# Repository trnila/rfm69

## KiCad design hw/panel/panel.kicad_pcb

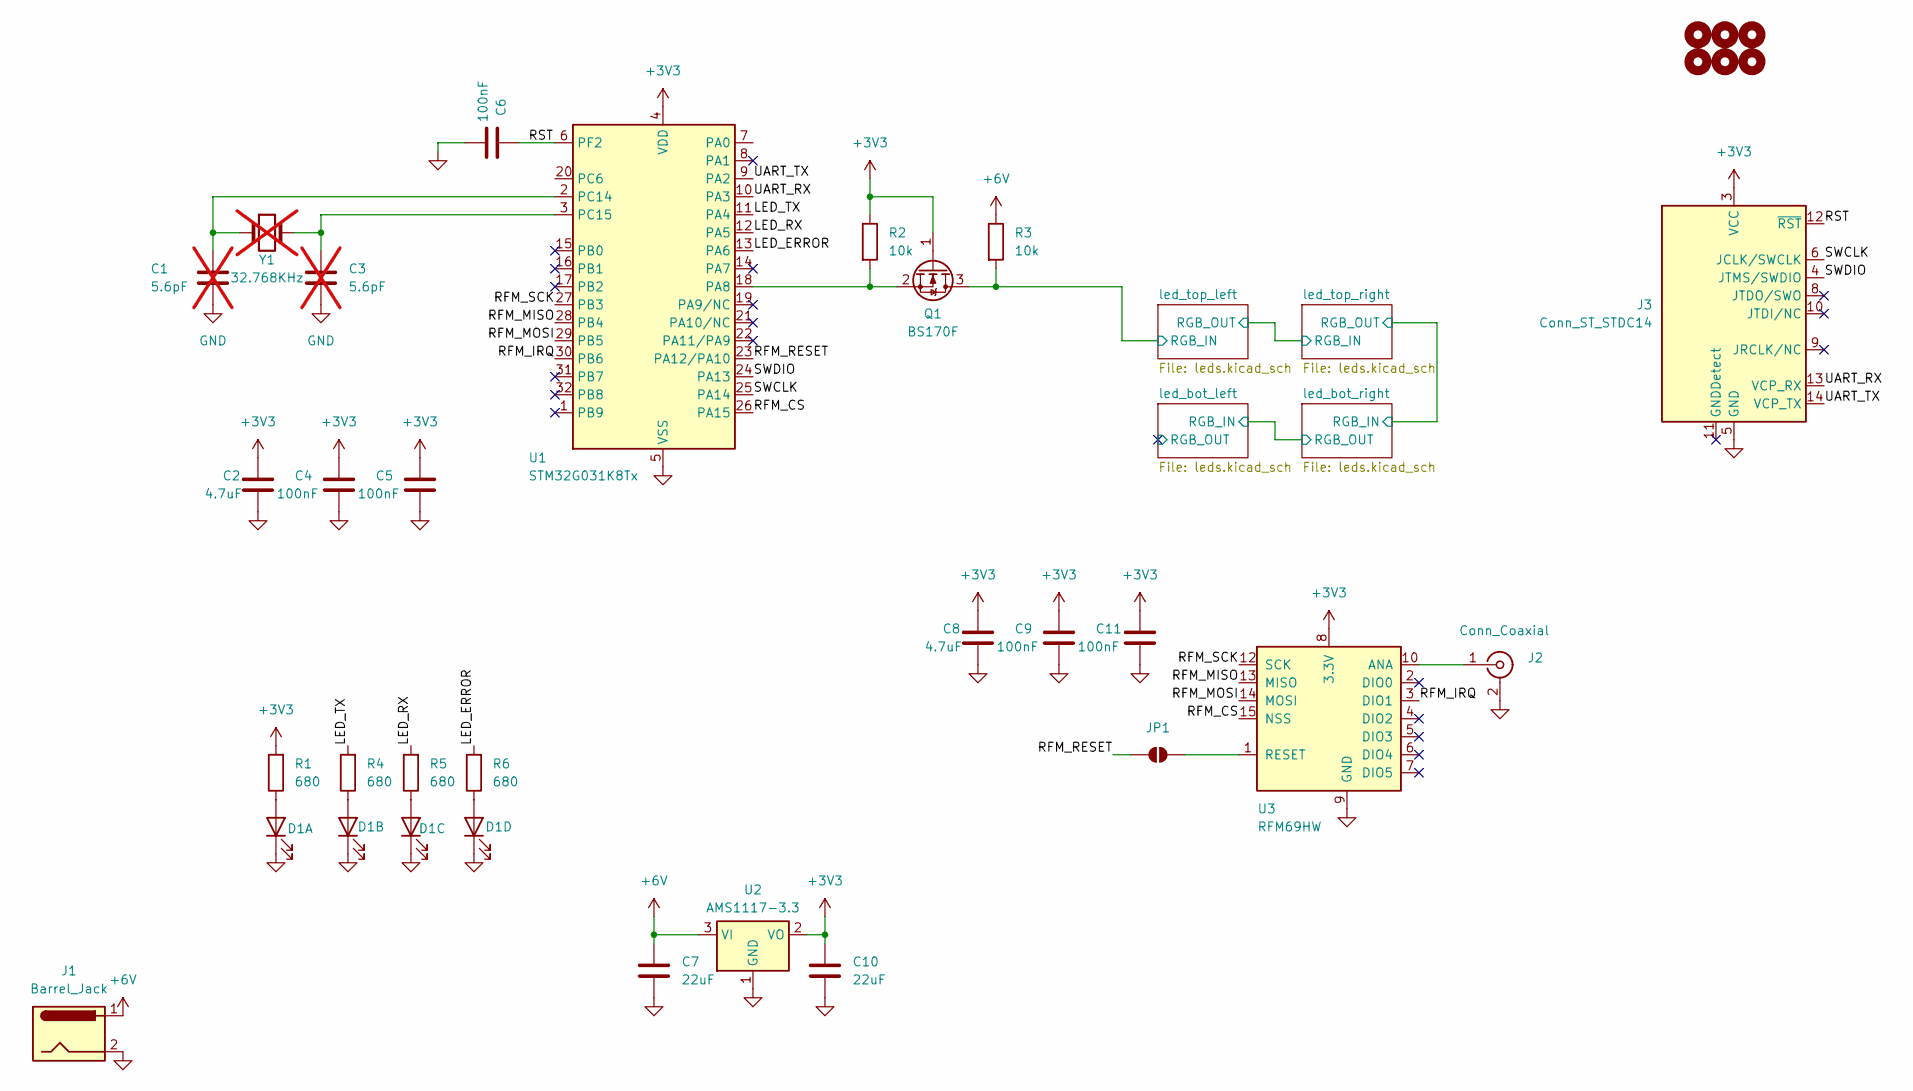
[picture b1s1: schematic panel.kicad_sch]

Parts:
C1, C3: 5.6pF; C_0805_2012Metric_Pad1.18x1.45mm_HandSolder; not fitted
C2, C8: 4.7uF; C_0805_2012Metric_Pad1.18x1.45mm_HandSolder
C4, C5, C6, C9, C11: 100nF; C_0805_2012Metric_Pad1.18x1.45mm_HandSolder
C7, C10: 22uF; C_1210_3225Metric
D1: light_guide
H1, H2, H3, H4, H200, H201: MountingHole; MountingHole_3.2mm_M3
J1: Barrel_Jack; Molex_Micro-Fit_3.0_43650-0200_1x02_P3.00mm_Horizontal
J2: Conn_Coaxial; SMA_Amphenol_901-143_Horizontal
J3: Conn_ST_STDC14; PinHeader_2x07_P1.27mm_Horizontal
JP1: SolderJumper_2_Bridged; SolderJumper-2_P1.3mm_Open_TrianglePad1.0x1.5mm
Q1: BS170F; SOT-23
R1, R4, R5, R6: 680; R_0805_2012Metric_Pad1.20x1.40mm_HandSolder
R2, R3: 10k; R_0805_2012Metric_Pad1.20x1.40mm_HandSolder
U1: STM32G031K8Tx; LQFP-32_7x7mm_P0.8mm
U2: AMS1117-3.3; SOT-223-3_TabPin2
U3: RFM69HW; HOPERF_RFM69HW
Y1: 32.768KHz; Crystal_SMD_3215-2Pin_3.2x1.5mm; not fitted

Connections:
+3V3: C2.1, C4.1, C5.1, C8.1, C9.1, C10.1, C11.1, J3.3 (VCC), Q1.1 (G), R1.2, R2.1, U1.4 (VDD), U2.2 (VO), U3.8 (3.3V)
+6V: C7.1, J1.1, R3.1, U2.3 (VI); also elsewhere on the board
/LED_ERROR: R6.2, U1.13 (PA6)
/LED_RX: R5.2, U1.12 (PA5)
/LED_TX: R4.2, U1.11 (PA4)
/RFM_CS: U1.26 (PA15), U3.15 (NSS)
/RFM_IRQ: U1.30 (PB6), U3.3 (DIO1)
/RFM_MISO: U1.28 (PB4), U3.13 (MISO)
/RFM_MOSI: U1.29 (PB5), U3.14 (MOSI)
/RFM_RESET: JP1.2 (B), U1.23 (PA12/PA10)
/RFM_SCK: U1.27 (PB3), U3.12 (SCK)
/RST: C6.1, J3.12 (~RST), U1.6 (PF2)
/SWCLK: J3.6 (JCLK/SWCLK), U1.25 (PA14)
/SWDIO: J3.4 (JTMS/SWDIO), U1.24 (PA13)
/UART_RX: J3.13 (VCP_RX), U1.10 (PA3)
/UART_TX: J3.14 (VCP_TX), U1.9 (PA2)
/led_top_left/RGB_IN: Q1.3 (D), R3.2; also elsewhere on the board
GND: C1.2, C2.2, C3.2, C4.2, C5.2, C6.2, C7.2, C8.2, C9.2, C10.2, C11.2, D1.1 (K), D1.3 (K), D1.5 (K), D1.7 (K), J1.2, J2.2 (Ext), J3.5 (GND), J3.7 (GND), U1.5 (VSS), U2.1 (GND), U3.9 (GND), U3.11 (GND); also elsewhere on the board
unnamed: D1.2 (A), R1.1
unnamed: D1.4 (A), R4.1
unnamed: D1.6 (A), R5.1
unnamed: D1.8 (A), R6.1
unnamed: J2.1 (In), U3.10 (ANA)
unnamed: JP1.1 (A), U3.1 (RESET)
unnamed: Q1.2 (S), R2.2, U1.18 (PA8)
unnamed: C1.1, U1.2 (PC14), Y1.1
unnamed: C3.1, U1.3 (PC15), Y1.2

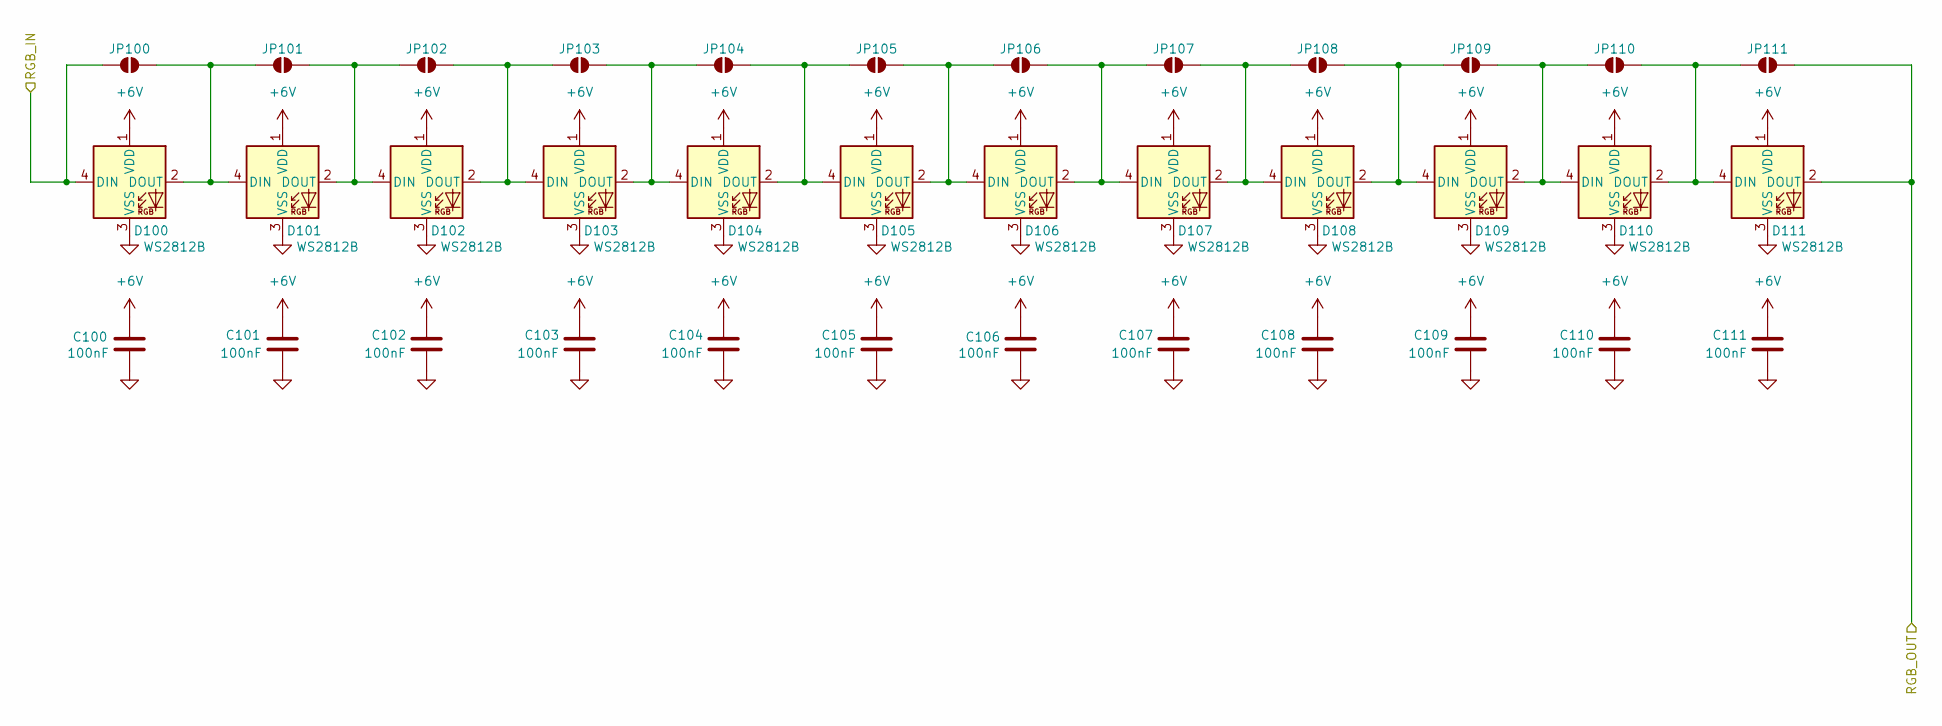
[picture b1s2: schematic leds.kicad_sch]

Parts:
C100, C101, C102, C103, C104, C105, C106, C107, C108, C109, C110, C111: 100nF; C_0805_2012Metric_Pad1.18x1.45mm_HandSolder
D100, D101, D102, D103, D104, D105, D106, D107, D108, D109, D110, D111: WS2812B; LED_WS2812B_PLCC4_5.0x5.0mm_P3.2mm
JP100, JP101, JP102, JP103, JP104, JP105, JP106, JP107, JP108, JP109, JP110, JP111: SolderJumper_2_Open; SolderJumper-2_P1.3mm_Open_TrianglePad1.0x1.5mm

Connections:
+6V: C100.1, C101.1, C102.1, C103.1, C104.1, C105.1, C106.1, C107.1, C108.1, C109.1, C110.1, C111.1, D100.1 (VDD), D101.1 (VDD), D102.1 (VDD), D103.1 (VDD), D104.1 (VDD), D105.1 (VDD), D106.1 (VDD), D107.1 (VDD), D108.1 (VDD), D109.1 (VDD), D110.1 (VDD), D111.1 (VDD); also elsewhere on the board
/led_top_left/RGB_IN: D100.4 (DIN), JP100.1 (A); also elsewhere on the board
/led_top_left/RGB_OUT: D111.2 (DOUT), JP111.2 (B); also elsewhere on the board
GND: C100.2, C101.2, C102.2, C103.2, C104.2, C105.2, C106.2, C107.2, C108.2, C109.2, C110.2, C111.2, D100.3 (VSS), D101.3 (VSS), D102.3 (VSS), D103.3 (VSS), D104.3 (VSS), D105.3 (VSS), D106.3 (VSS), D107.3 (VSS), D108.3 (VSS), D109.3 (VSS), D110.3 (VSS), D111.3 (VSS); also elsewhere on the board
unnamed: D100.2 (DOUT), D101.4 (DIN), JP100.2 (B), JP101.1 (A)
unnamed: D101.2 (DOUT), D102.4 (DIN), JP101.2 (B), JP102.1 (A)
unnamed: D102.2 (DOUT), D103.4 (DIN), JP102.2 (B), JP103.1 (A)
unnamed: D103.2 (DOUT), D104.4 (DIN), JP103.2 (B), JP104.1 (A)
unnamed: D104.2 (DOUT), D105.4 (DIN), JP104.2 (B), JP105.1 (A)
unnamed: D105.2 (DOUT), D106.4 (DIN), JP105.2 (B), JP106.1 (A)
unnamed: D106.2 (DOUT), D107.4 (DIN), JP106.2 (B), JP107.1 (A)
unnamed: D107.2 (DOUT), D108.4 (DIN), JP107.2 (B), JP108.1 (A)
unnamed: D108.2 (DOUT), D109.4 (DIN), JP108.2 (B), JP109.1 (A)
unnamed: D109.2 (DOUT), D110.4 (DIN), JP109.2 (B), JP110.1 (A)
unnamed: D110.2 (DOUT), D111.4 (DIN), JP110.2 (B), JP111.1 (A)

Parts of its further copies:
C112, C113, C114, C115, C116, C117, C118, C119, C120, C121, C122, C123, C200, C201, C202, C203, C204, C205, C206, C207, C208, C209, C210, C211, C212, C213, C214, C215, C216, C217, C218, C219, C220, C221, C222, C223: 100nF; C_0805_2012Metric_Pad1.18x1.45mm_HandSolder
D112, D113, D114, D115, D116, D117, D118, D119, D120, D121, D122, D123, D200, D201, D202, D203, D204, D205, D206, D207, D208, D209, D210, D211, D212, D213, D214, D215, D216, D217, D218, D219, D220, D221, D222, D223: WS2812B; LED_WS2812B_PLCC4_5.0x5.0mm_P3.2mm
JP112, JP113, JP114, JP115, JP116, JP117, JP118, JP119, JP120, JP121, JP122, JP123, JP200, JP201, JP202, JP203, JP204, JP205, JP206, JP207, JP208, JP209, JP210, JP211, JP212, JP213, JP214, JP215, JP216, JP217, JP218, JP219, JP220, JP221, JP222, JP223: SolderJumper_2_Open; SolderJumper-2_P1.3mm_Open_TrianglePad1.0x1.5mm

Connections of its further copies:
+6V: C112.1, C113.1, C114.1, C115.1, C116.1, C117.1, C118.1, C119.1, C120.1, C121.1, C122.1, C123.1, C200.1, C201.1, C202.1, C203.1, C204.1, C205.1, C206.1, C207.1, C208.1, C209.1, C210.1, C211.1, C212.1, C213.1, C214.1, C215.1, C216.1, C217.1, C218.1, C219.1, C220.1, C221.1, C222.1, C223.1, D112.1 (VDD), D113.1 (VDD), D114.1 (VDD), D115.1 (VDD), D116.1 (VDD), D117.1 (VDD), D118.1 (VDD), D119.1 (VDD), D120.1 (VDD), D121.1 (VDD), D122.1 (VDD), D123.1 (VDD), D200.1 (VDD), D201.1 (VDD), D202.1 (VDD), D203.1 (VDD), D204.1 (VDD), D205.1 (VDD), D206.1 (VDD), D207.1 (VDD), D208.1 (VDD), D209.1 (VDD), D210.1 (VDD), D211.1 (VDD), D212.1 (VDD), D213.1 (VDD), D214.1 (VDD), D215.1 (VDD), D216.1 (VDD), D217.1 (VDD), D218.1 (VDD), D219.1 (VDD), D220.1 (VDD), D221.1 (VDD), D222.1 (VDD), D223.1 (VDD); also elsewhere on the board
/led_bot_left/RGB_IN: D211.2 (DOUT), D212.4 (DIN), JP211.2 (B), JP212.1 (A)
/led_bot_left/RGB_OUT: D223.2 (DOUT), JP223.2 (B)
/led_bot_right/RGB_IN: D123.2 (DOUT), D200.4 (DIN), JP123.2 (B), JP200.1 (A)
/led_top_left/RGB_OUT: D112.4 (DIN), JP112.1 (A); also elsewhere on the board
GND: C112.2, C113.2, C114.2, C115.2, C116.2, C117.2, C118.2, C119.2, C120.2, C121.2, C122.2, C123.2, C200.2, C201.2, C202.2, C203.2, C204.2, C205.2, C206.2, C207.2, C208.2, C209.2, C210.2, C211.2, C212.2, C213.2, C214.2, C215.2, C216.2, C217.2, C218.2, C219.2, C220.2, C221.2, C222.2, C223.2, D112.3 (VSS), D113.3 (VSS), D114.3 (VSS), D115.3 (VSS), D116.3 (VSS), D117.3 (VSS), D118.3 (VSS), D119.3 (VSS), D120.3 (VSS), D121.3 (VSS), D122.3 (VSS), D123.3 (VSS), D200.3 (VSS), D201.3 (VSS), D202.3 (VSS), D203.3 (VSS), D204.3 (VSS), D205.3 (VSS), D206.3 (VSS), D207.3 (VSS), D208.3 (VSS), D209.3 (VSS), D210.3 (VSS), D211.3 (VSS), D212.3 (VSS), D213.3 (VSS), D214.3 (VSS), D215.3 (VSS), D216.3 (VSS), D217.3 (VSS), D218.3 (VSS), D219.3 (VSS), D220.3 (VSS), D221.3 (VSS), D222.3 (VSS), D223.3 (VSS); also elsewhere on the board
unnamed: D112.2 (DOUT), D113.4 (DIN), JP112.2 (B), JP113.1 (A)
unnamed: D113.2 (DOUT), D114.4 (DIN), JP113.2 (B), JP114.1 (A)
unnamed: D114.2 (DOUT), D115.4 (DIN), JP114.2 (B), JP115.1 (A)
unnamed: D115.2 (DOUT), D116.4 (DIN), JP115.2 (B), JP116.1 (A)
unnamed: D116.2 (DOUT), D117.4 (DIN), JP116.2 (B), JP117.1 (A)
unnamed: D117.2 (DOUT), D118.4 (DIN), JP117.2 (B), JP118.1 (A)
unnamed: D118.2 (DOUT), D119.4 (DIN), JP118.2 (B), JP119.1 (A)
unnamed: D119.2 (DOUT), D120.4 (DIN), JP119.2 (B), JP120.1 (A)
unnamed: D120.2 (DOUT), D121.4 (DIN), JP120.2 (B), JP121.1 (A)
unnamed: D121.2 (DOUT), D122.4 (DIN), JP121.2 (B), JP122.1 (A)
unnamed: D122.2 (DOUT), D123.4 (DIN), JP122.2 (B), JP123.1 (A)
unnamed: D200.2 (DOUT), D201.4 (DIN), JP200.2 (B), JP201.1 (A)
unnamed: D201.2 (DOUT), D202.4 (DIN), JP201.2 (B), JP202.1 (A)
unnamed: D202.2 (DOUT), D203.4 (DIN), JP202.2 (B), JP203.1 (A)
unnamed: D203.2 (DOUT), D204.4 (DIN), JP203.2 (B), JP204.1 (A)
unnamed: D204.2 (DOUT), D205.4 (DIN), JP204.2 (B), JP205.1 (A)
unnamed: D205.2 (DOUT), D206.4 (DIN), JP205.2 (B), JP206.1 (A)
unnamed: D206.2 (DOUT), D207.4 (DIN), JP206.2 (B), JP207.1 (A)
unnamed: D207.2 (DOUT), D208.4 (DIN), JP207.2 (B), JP208.1 (A)
unnamed: D208.2 (DOUT), D209.4 (DIN), JP208.2 (B), JP209.1 (A)
unnamed: D209.2 (DOUT), D210.4 (DIN), JP209.2 (B), JP210.1 (A)
unnamed: D210.2 (DOUT), D211.4 (DIN), JP210.2 (B), JP211.1 (A)
unnamed: D212.2 (DOUT), D213.4 (DIN), JP212.2 (B), JP213.1 (A)
unnamed: D213.2 (DOUT), D214.4 (DIN), JP213.2 (B), JP214.1 (A)
unnamed: D214.2 (DOUT), D215.4 (DIN), JP214.2 (B), JP215.1 (A)
unnamed: D215.2 (DOUT), D216.4 (DIN), JP215.2 (B), JP216.1 (A)
unnamed: D216.2 (DOUT), D217.4 (DIN), JP216.2 (B), JP217.1 (A)
unnamed: D217.2 (DOUT), D218.4 (DIN), JP217.2 (B), JP218.1 (A)
unnamed: D218.2 (DOUT), D219.4 (DIN), JP218.2 (B), JP219.1 (A)
unnamed: D219.2 (DOUT), D220.4 (DIN), JP219.2 (B), JP220.1 (A)
unnamed: D220.2 (DOUT), D221.4 (DIN), JP220.2 (B), JP221.1 (A)
unnamed: D221.2 (DOUT), D222.4 (DIN), JP221.2 (B), JP222.1 (A)
unnamed: D222.2 (DOUT), D223.4 (DIN), JP222.2 (B), JP223.1 (A)

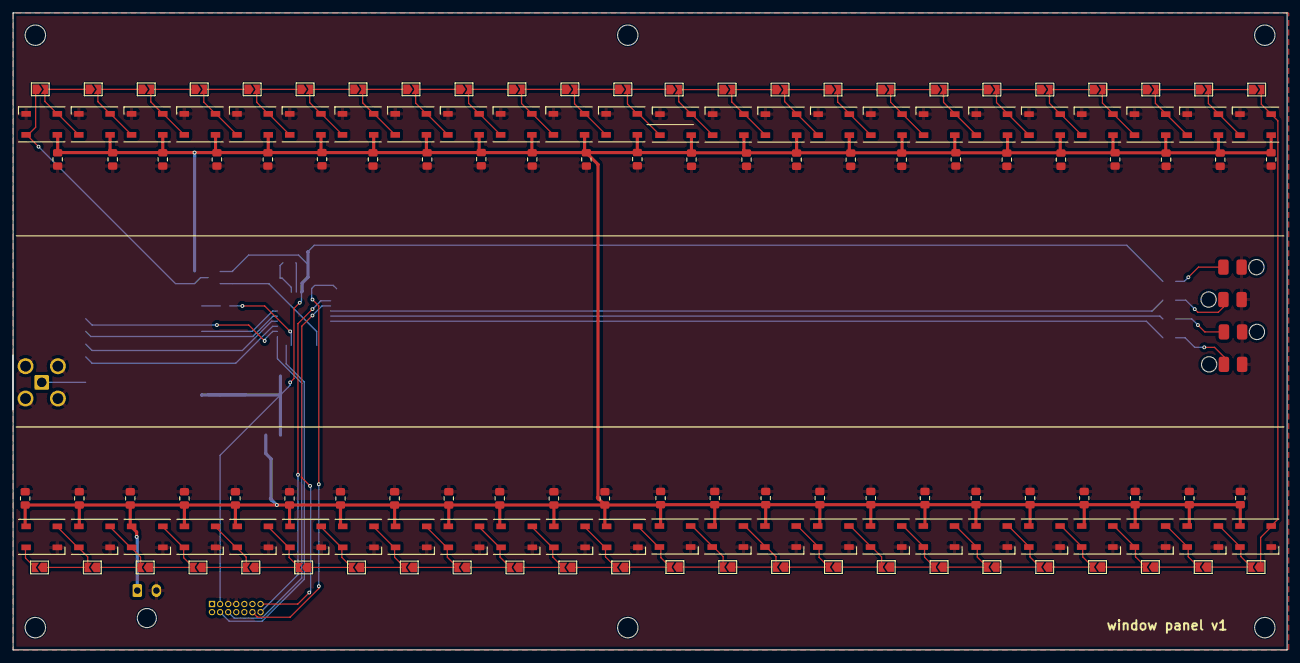
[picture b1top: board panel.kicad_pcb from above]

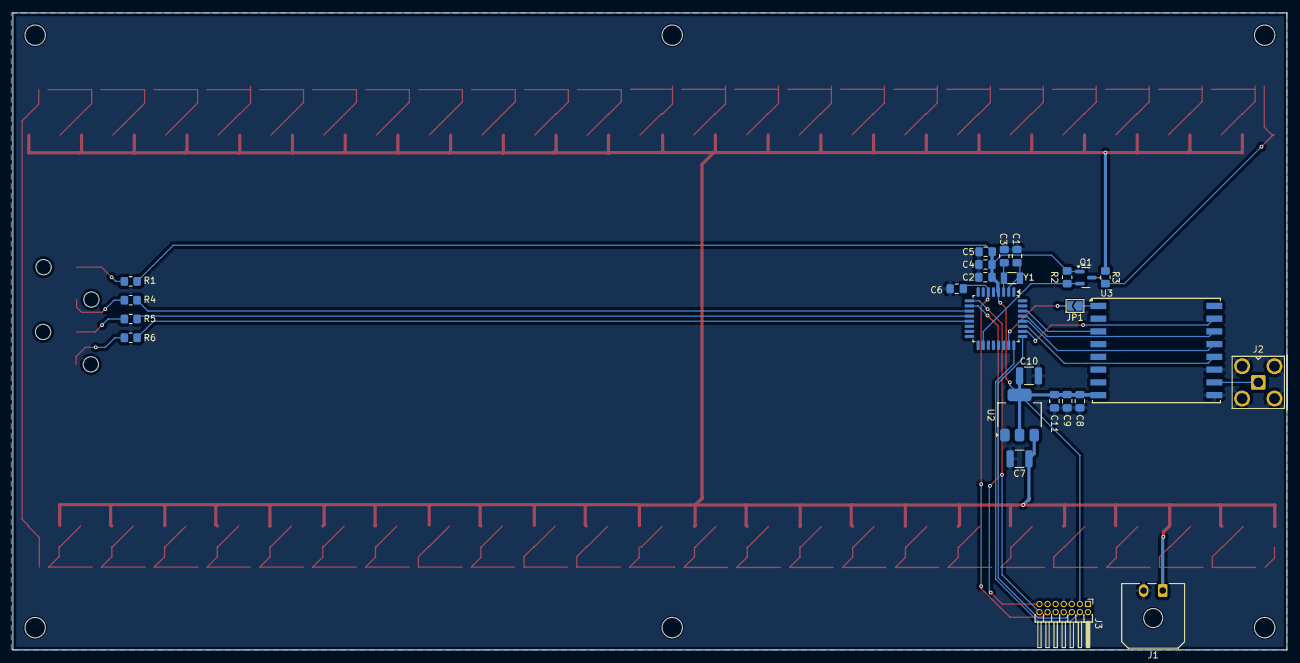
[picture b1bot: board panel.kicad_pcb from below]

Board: 2 copper layers, 200.0 x 99.9 mm, 177 parts (26 on the bottom side), 75 nets.

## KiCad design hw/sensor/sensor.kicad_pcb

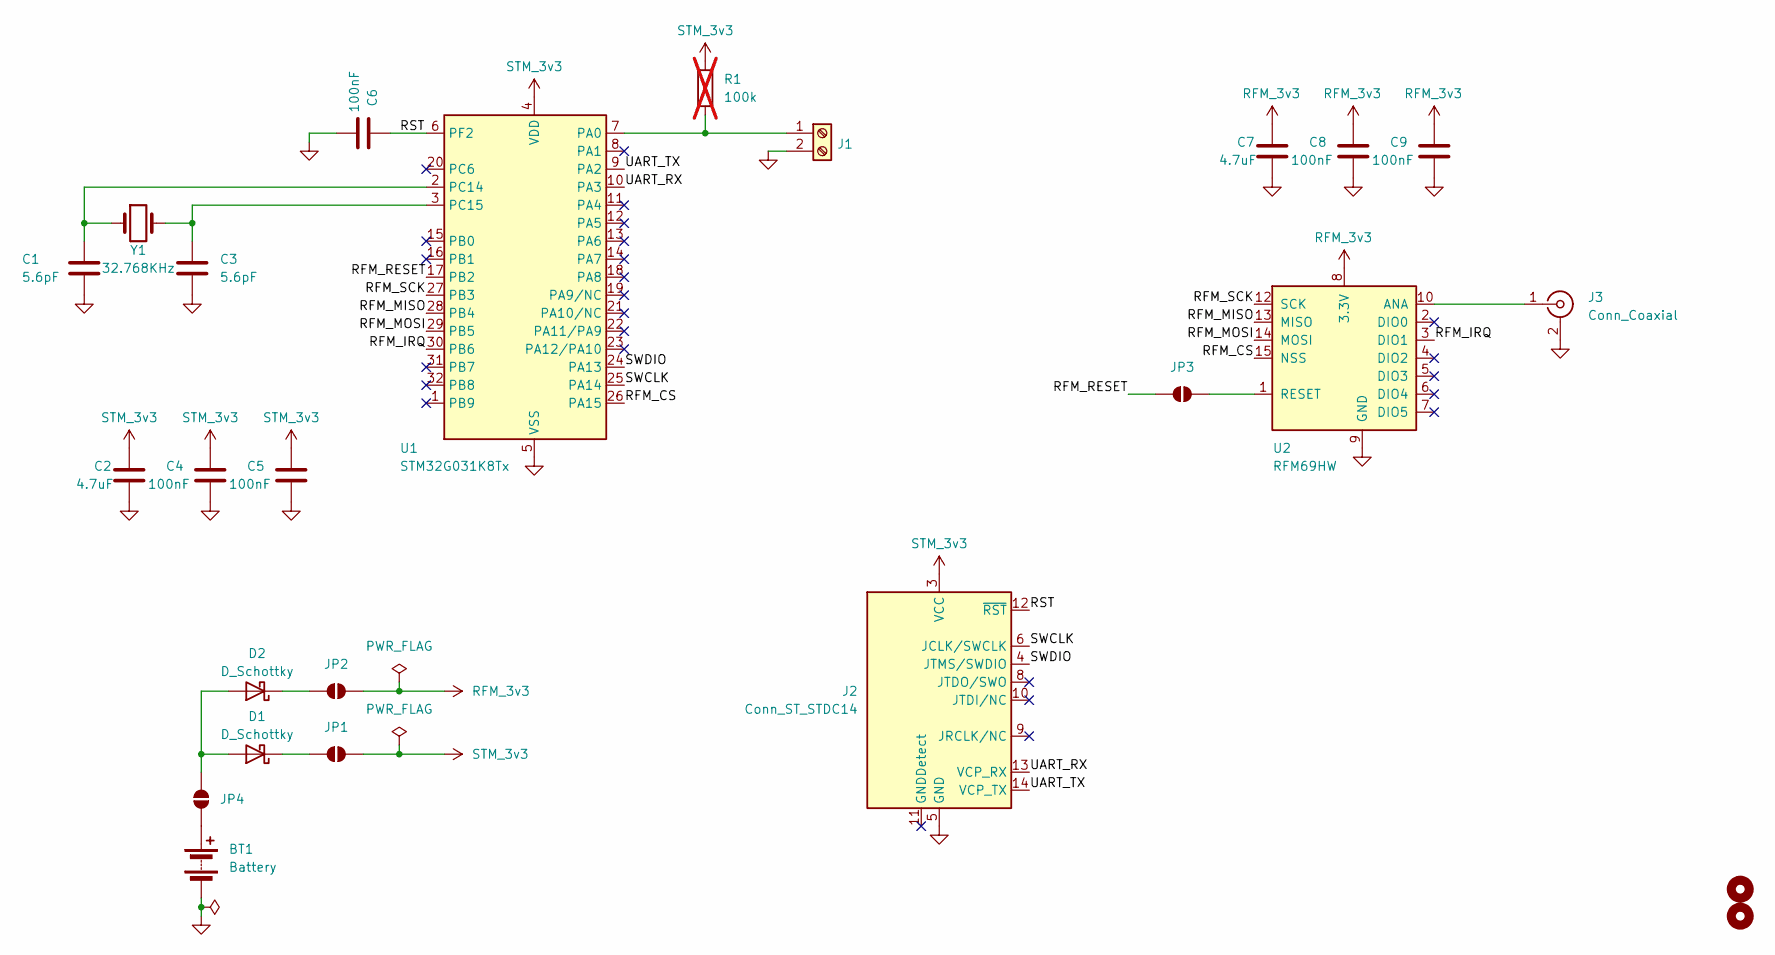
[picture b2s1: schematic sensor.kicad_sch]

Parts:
BT1: Battery; BatteryHolder_Keystone_2462_2xAA
C1, C3: 5.6pF; C_0805_2012Metric_Pad1.18x1.45mm_HandSolder
C2, C7: 4.7uF; C_0805_2012Metric_Pad1.18x1.45mm_HandSolder
C4, C5, C6, C8, C9: 100nF; C_0805_2012Metric_Pad1.18x1.45mm_HandSolder
D1, D2: D_Schottky; D_SOD-323_HandSoldering
H1, H4: MountingHole; MountingHole_3.2mm_M3
J1: Screw_Terminal_01x02; TerminalBlock_Xinya_XY308-2.54-2P_1x02_P2.54mm_Horizontal
J2: Conn_ST_STDC14; PinHeader_2x07_P1.27mm_Vertical
J3: Conn_Coaxial; SMA_Amphenol_901-143_Horizontal
JP1, JP2, JP3, JP4: SolderJumper_2_Bridged; SolderJumper-2_P1.3mm_Open_TrianglePad1.0x1.5mm
R1: 100k; R_0805_2012Metric_Pad1.20x1.40mm_HandSolder; not fitted
U1: STM32G031K8Tx; LQFP-32_7x7mm_P0.8mm
U2: RFM69HW; HOPERF_RFM69HW
Y1: 32.768KHz; Crystal_SMD_3215-2Pin_3.2x1.5mm

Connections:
/RFM_CS: U1.26 (PA15), U2.15 (NSS)
/RFM_IRQ: U1.30 (PB6), U2.3 (DIO1)
/RFM_MISO: U1.28 (PB4), U2.13 (MISO)
/RFM_MOSI: U1.29 (PB5), U2.14 (MOSI)
/RFM_RESET: JP3.2 (B), U1.17 (PB2)
/RFM_SCK: U1.27 (PB3), U2.12 (SCK)
/RST: C6.1, J2.12 (~RST), U1.6 (PF2)
/SWCLK: J2.6 (JCLK/SWCLK), U1.25 (PA14)
/SWDIO: J2.4 (JTMS/SWDIO), U1.24 (PA13)
/UART_RX: J2.13 (VCP_RX), U1.10 (PA3)
/UART_TX: J2.14 (VCP_TX), U1.9 (PA2)
GND: BT1.2 (-), C1.2, C2.2, C3.2, C4.2, C5.2, C6.2, C7.2, C8.2, C9.2, J1.2, J2.5 (GND), J2.7 (GND), J3.2 (Ext), U1.5 (VSS), U2.9 (GND), U2.11 (GND)
unnamed: BT1.1 (+), JP4.1 (A)
unnamed: D1.2 (A), D2.2 (A), JP4.2 (B)
unnamed: D1.1 (K), JP1.2 (B)
unnamed: D2.1 (K), JP2.2 (B)
unnamed: J1.1, R1.2, U1.7 (PA0)
unnamed: J3.1 (In), U2.10 (ANA)
unnamed: JP3.1 (A), U2.1 (RESET)
unnamed: C1.1, U1.2 (PC14), Y1.1
unnamed: C3.1, U1.3 (PC15), Y1.2
RFM_3v3: C7.1, C8.1, C9.1, JP2.1 (A), U2.8 (3.3V)
STM_3v3: C2.1, C4.1, C5.1, J2.3 (VCC), JP1.1 (A), R1.1, U1.4 (VDD)

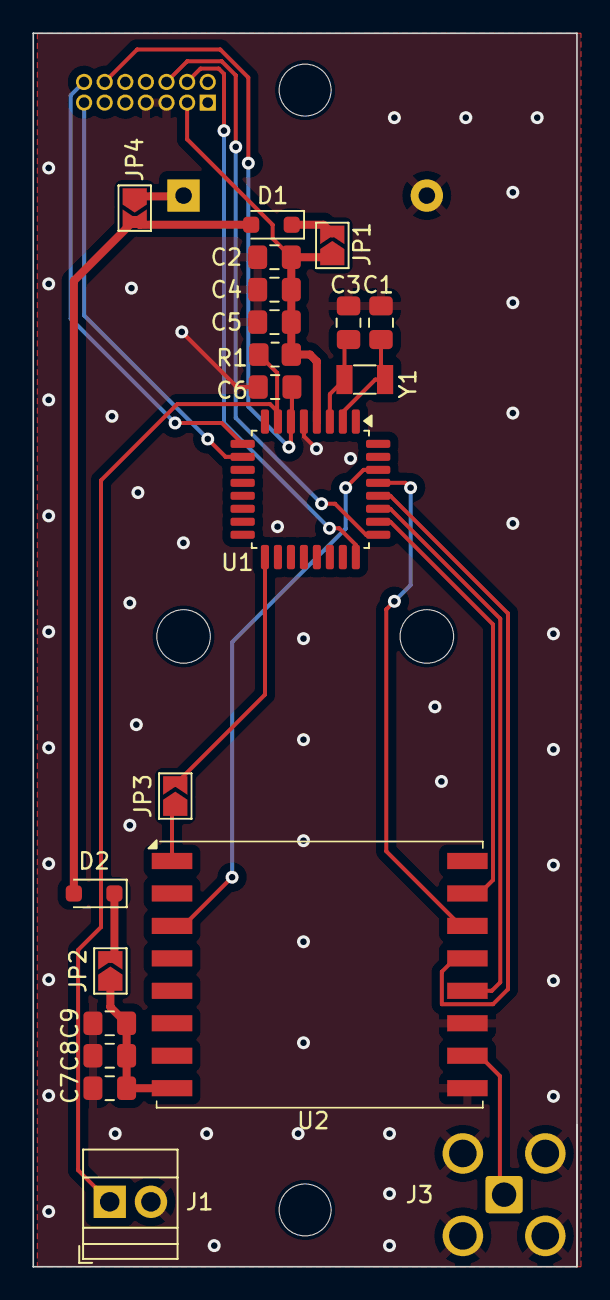
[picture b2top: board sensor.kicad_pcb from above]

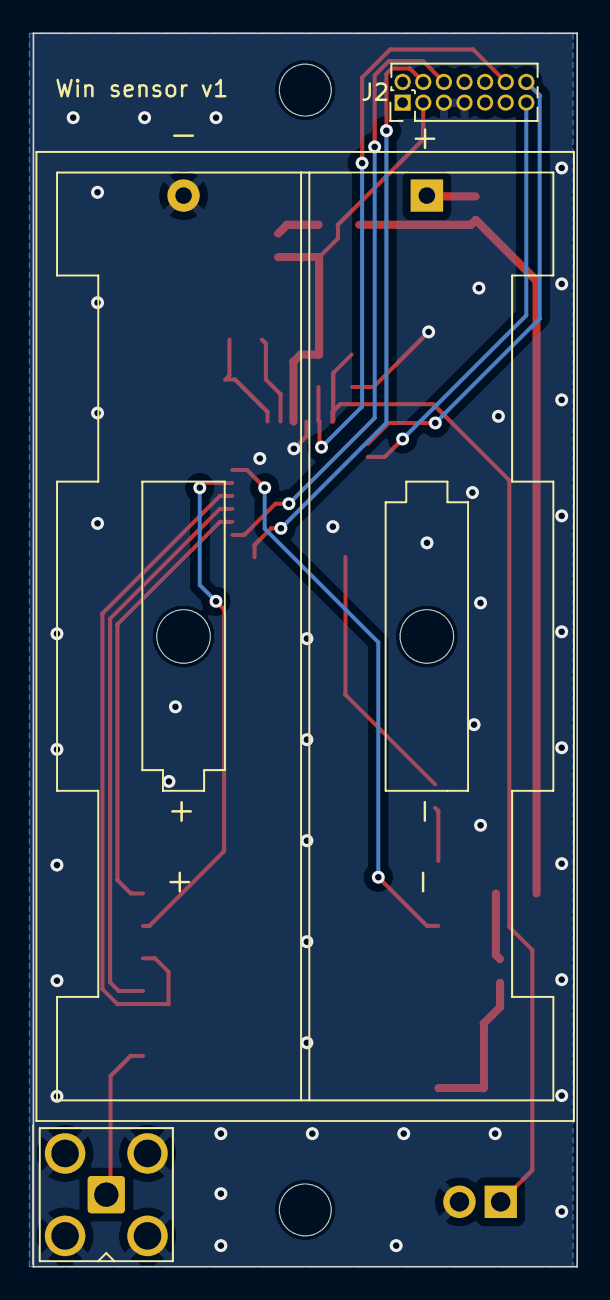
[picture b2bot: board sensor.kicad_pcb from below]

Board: 2 copper layers, 33.5 x 76.0 mm, 25 parts (3 on the bottom side), 23 nets.

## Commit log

2023-11-02 RFM69: defined packet structure
2023-11-02 RFM69: node filtering
2023-11-02 RFM69: using irq
2023-11-12 gw.py: support cover sensors
2023-11-12 rgb: send signal only on change and if there is no pending DMA request
2023-11-12 rgb: removed floats to reduce code size
2023-11-12 gpio: added reading input
2023-11-12 gpio: configurable pullup/down
2023-11-12 timers: added initial impl
2023-11-12 RFM69: async DMA implementation with ack and retransmissions
2023-11-12 receiver: show opened windows on RGB strip
2023-11-12 sensor: use timer instead of loop count
    timer header
    x
2023-11-12 sensor: added window sensor
2023-11-12 Send and receive multiple sensors in one radio packet
2023-11-13 Config can be flashed into dedicated flash section
2023-11-20 tool.py: unified flashing and parameters configuration into single tool
2023-11-20 Added all devices into .vscode/launch.json
2023-11-25 Removed shared main function
2023-11-25 Run sensor on 1Mhz clock
2023-11-25 Wake sensor
2023-11-26 UART: configurable clock in and baud rate
2023-12-05 wake up pin
2023-12-12 Use PA0 for window sensor
2023-12-12 window sensor: go to shutdown after window was closed/opened and periodically
2024-07-20 Replace after-main infinite loop with [[noreturn]]
2024-07-20 Added CI for building
2024-07-20 CI: run pre-commit
2024-07-20 Added sensor hw
2024-07-20 new version of kicad
2024-07-20 removed step-up, using direct VBAT
2024-07-20 debugging connectors unified to one
2024-07-21 change
2024-07-21 Send custom message
2024-07-21 tool.py: openocd connects under reset because of deep sleep sensor
2024-07-21 Added forgotten protocol
2024-07-21 adc: fixed vbat reading
2024-07-21 adc: simplified
2024-07-21 adc: removed unused channels
2024-07-21 adc: read temp
2024-07-21 moved wakeup to PA0
2024-07-21 wakeup: use just one wakeup pin and set oposite level then we have sent
2024-07-21 receiver: show state of window again
2024-07-21 receiver: removed commented code
2024-07-21 receiver: increased timeout to match value from sensors
2024-07-21 pin: use pull-up in shutdown
2024-07-21 optional external pull-up for sensor pin
2024-07-22 tool.py: added gdb command for debugging
2024-07-22 Keepalive tolerance is shared between receiver and sensor
2024-07-22 RFM69: simplified blocking
2024-07-22 RFM69: removed async
2024-07-22 RFM69: fixed states
2024-07-22 send ack
2024-07-22 RSSI testing
2024-07-22 counters
2024-07-24 Registers for MAX tx power
2024-07-24 Added docker
2024-07-24 lowered timeout
2024-07-24 weird fix
2024-07-24 Added missing reg
2024-07-25 docker: network host
2024-07-25 pcb updated
2024-07-25 Removed shellcheck
2024-07-25 First PCB
2024-07-25 models
2024-07-25 renamed and moved
2024-07-25 deleted
2024-07-25 Added pannel
2024-07-26 sensor redesigned
2024-07-26 panel
2024-07-28 panel progress
2024-07-28 Added light guide lib
2024-07-28 extend top to 200mm
2024-07-28 bot left
2024-07-28 Added bot right
2024-07-28 optimized paths
2024-07-28 holes
